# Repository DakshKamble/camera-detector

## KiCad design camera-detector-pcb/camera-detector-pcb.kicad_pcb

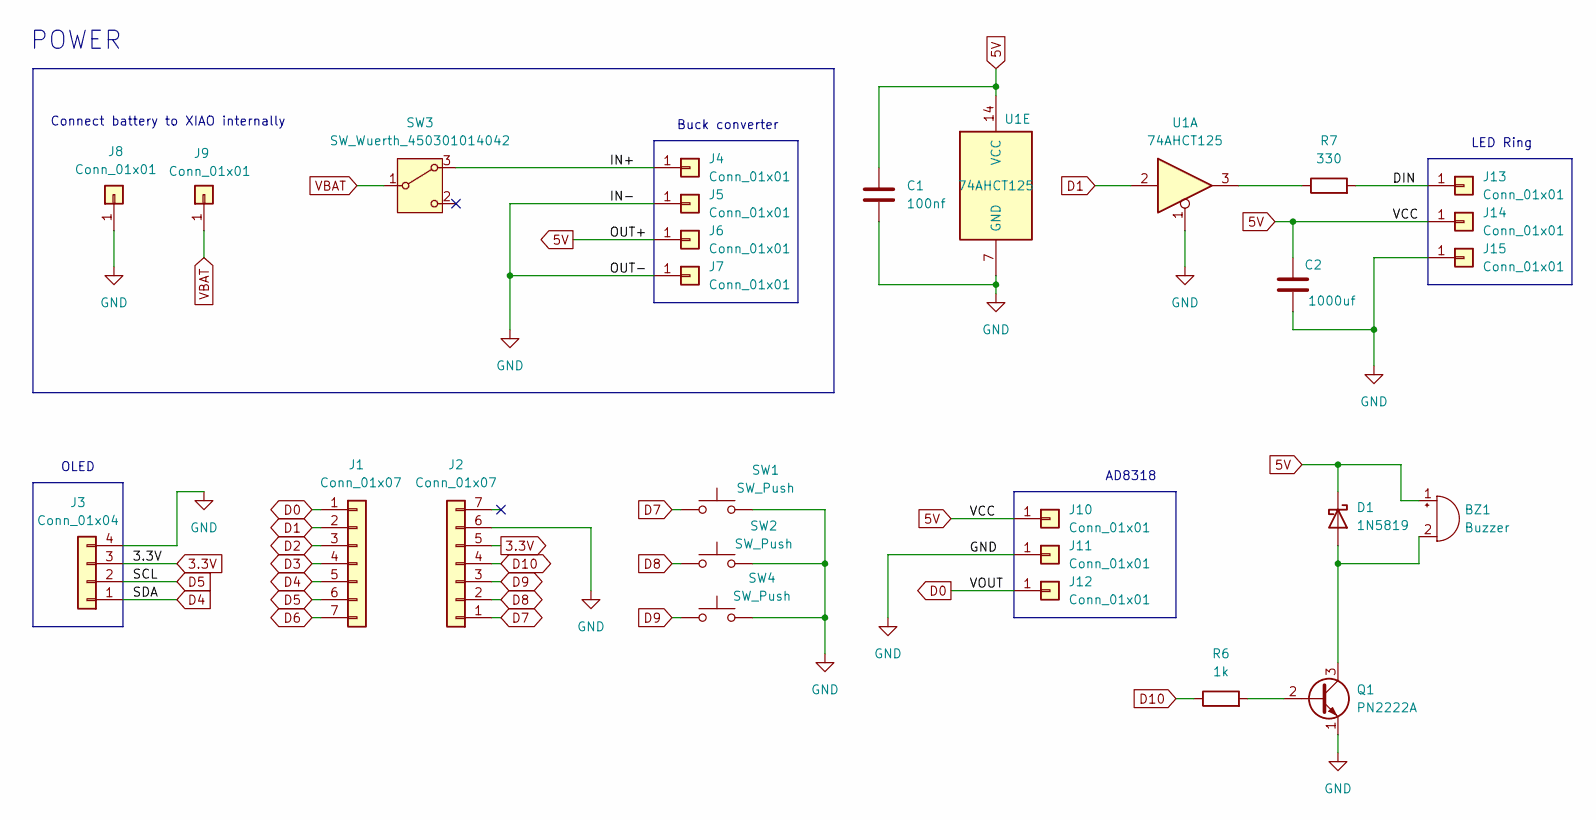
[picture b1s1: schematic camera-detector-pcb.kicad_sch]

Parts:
BZ1: Buzzer; Buzzer_15x7.5RM7.6
C1: 100nf; C_Disc_D3.0mm_W1.6mm_P2.50mm
C2: 1000uf; CP_Radial_D10.0mm_P5.00mm
D1: 1N5819; D_DO-41_SOD81_P10.16mm_Horizontal
J1, J2: Conn_01x07; PinSocket_1x07_P2.54mm_Vertical
J3: Conn_01x04; PinSocket_1x04_P2.54mm_Vertical
J4, J5, J6, J7, J10, J11, J12, J13, J14, J15: Conn_01x01; PinHeader_1x01_P2.54mm_Vertical
J8, J9: Conn_01x01; PinSocket_1x01_P2.00mm_Vertical
Q1: PN2222A; TO-92_Inline_Wide
R6: 1k; R_Axial_DIN0204_L3.6mm_D1.6mm_P5.08mm_Horizontal
R7: 330; R_Axial_DIN0204_L3.6mm_D1.6mm_P5.08mm_Horizontal
SW1, SW2, SW4: SW_Push; SW_PUSH_6mm
SW3: SW_Wuerth_450301014042; SW_Slide-03_Wuerth-WS-SLTV_10x2.5x6.4_P2.54mm
U1: 74AHCT125; CERDIP-14_W7.62mm_SideBrazed

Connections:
3.3V: J2.5, J3.3
5V: BZ1.1 (+), C1.1, C2.1, D1.1 (K), J6.1 (Pin_1_1), J10.1 (Pin_1_1), J14.1 (Pin_1_1), U1.14 (VCC)
/DIN: J13.1 (Pin_1_1), R7.2
/IN+: J4.1 (Pin_1_1), SW3.3 (A)
D0: J1.1, J12.1 (Pin_1_1)
D1: J1.2, U1.2
D2: J1.3
D3: J1.4
D4: J1.5, J3.1
D5: J1.6, J3.2
D6: J1.7
D7: J2.1, SW1.1
D8: J2.2, SW2.1
D9: J2.3, SW4.1
D10: J2.4, R6.1
GND: C1.2, C2.2, J2.6, J3.4, J5.1 (Pin_1_1), J7.1 (Pin_1_1), J8.1 (Pin_1_1), J11.1 (Pin_1_1), J15.1 (Pin_1_1), Q1.1 (E), SW1.2, SW2.2, SW4.2, U1.1, U1.7 (GND)
unnamed: BZ1.2 (-), D1.2 (A), Q1.3 (C)
unnamed: Q1.2 (B), R6.2
unnamed: R7.1, U1.3
VBAT: J9.1 (Pin_1_1), SW3.1 (B)

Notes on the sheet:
OLED
AD8318
Buck converter
POWER
LED Ring
Connect battery to XIAO internally

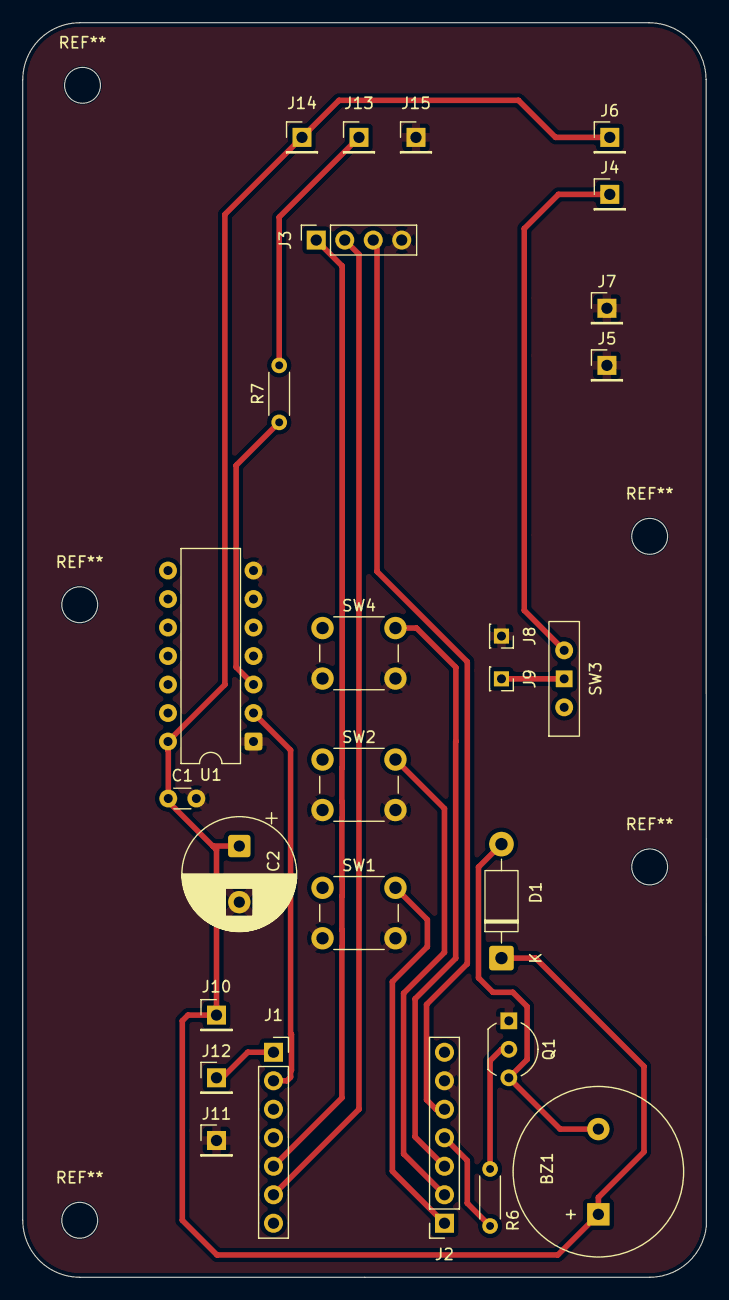
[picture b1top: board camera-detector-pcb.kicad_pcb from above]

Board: 2 copper layers, 60.9 x 111.8 mm, 27 parts (0 on the bottom side), 17 nets.
